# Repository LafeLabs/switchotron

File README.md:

# [SWITCHOTRON](https://github.com/lafelabs/switchotron/)

### [localhost](http://localhost/)

## 6 channel switch control code:

```

#include <Adafruit_NeoPixel.h>
#ifdef __AVR__
#endif

// Which pin on the Arduino is connected to the NeoPixels?
#define PIN        12 // On Trinket or Gemma, suggest changing this to 1

// How many NeoPixels are attached to the Arduino?
#define NUMPIXELS 6 // Popular NeoPixel ring size
//there are 8 neopixels but this code is for 6 used along with 6 buttons

// When setting up the NeoPixel library, we tell it how many pixels,  
// and which pin to use to send signals. Note that for older NeoPixel
// strips you might need to change the third parameter -- see the
// strandtest example for more information on possible values.
Adafruit_NeoPixel pixels(NUMPIXELS, PIN, NEO_GRB + NEO_KHZ800);

int analog = 0;
int delta = 100;
int mode = 1;//modes are 1,2,3,4,5, and 6 which are pixel 5,4,3,2,1, and 0 respectively

void setup() {
   Serial.begin(115200);

  // These lines are specifically to support the Adafruit Trinket 5V 16 MHz.
  // Any other board, you can remove this part (but no harm leaving it):
#if defined(__AVR_ATtiny85__) && (F_CPU == 16000000)
  clock_prescale_set(clock_div_1);
#endif
  // END of Trinket-specific code.

    pinMode(3,OUTPUT);
    pinMode(4,OUTPUT);
    pinMode(5,OUTPUT);
    pinMode(6,OUTPUT);
    pinMode(7,OUTPUT);
    pinMode(8,OUTPUT);

    digitalWrite(3,LOW);
    digitalWrite(4,LOW);
    digitalWrite(5,LOW);
    digitalWrite(6,LOW);
    digitalWrite(7,LOW);
    digitalWrite(8,LOW);

  pixels.begin(); // INITIALIZE NeoPixel strip object (REQUIRED)

}

void loop() {
  pixels.clear(); // Set all pixel colors to 'off'
  analog = analogRead(A0);
  // The first NeoPixel in a strand is #0, second is 1, all the way up
  // to the count of pixels minus one.
  
  if(analog > 1024 - delta){
    delay(1);
    analog = analogRead(A0);
    if(analog > 1023 - delta){
       mode = 1;      
    }
  }
  if(analog > 781 - delta && analog < 781 + delta){
    delay(5);
    analog = analogRead(A0);
    if(analog > 781 - delta && analog < 781 + delta){
         mode = 2; 
    }
  }
  if(analog > 593 - delta && analog < 593 + delta){
     delay(5);
     analog = analogRead(A0);

    if(analog > 593 - delta && analog < 593 + delta){
      mode = 3;    
    }
  }

  if(analog > 436 - delta && analog < 436 + delta){
     delay(1);
     analog = analogRead(A0);

    if(analog > 436 - delta && analog < 436 + delta){
      mode = 4;    
    }
  }

  if(analog > 296 - delta && analog < 296 + delta){
     delay(1);
     analog = analogRead(A0);

    if(analog > 296 - delta && analog < 296 + delta){
      mode = 5;    
    }
  }

  if(analog > 154 - delta && analog < 154 + delta){
     delay(1);
     analog = analogRead(A0);

    if(analog > 154 - delta && analog < 154 + delta){
      mode = 6;    
    }
  }

  if (Serial.available()) {

    //for more info on this code see http://adam-meyer.com/arduino/arduino-serial
    //read serial as ascii integer
        int ser = Serial.read();
    //    Serial.println(ser);
     if(ser == 49){    //ASCII for 1
      mode = 1;
     }
     if(ser == 50){    //ASCII for 2
      mode = 2;
     }
     if(ser == 51){    //ASCII for 3
      mode = 3;
     }
     if(ser == 52){    //ASCII for 4
      mode = 4;
     }
     if(ser == 53){    //ASCII for 5
      mode = 5;
     }
     if(ser == 54){    //ASCII for 6
      mode = 6;
     }

  }

  if(mode == 1){
    pixels.setPixelColor(0, pixels.Color(0, 0, 0));    
    pixels.setPixelColor(1, pixels.Color(0, 0, 0));    
    pixels.setPixelColor(2, pixels.Color(0, 0, 0));    
    pixels.setPixelColor(3, pixels.Color(0, 0, 0));    
    pixels.setPixelColor(4, pixels.Color(0, 0, 0));    
    pixels.setPixelColor(5, pixels.Color(255, 0, 0));    

    digitalWrite(3,HIGH);
    digitalWrite(4,LOW);
    digitalWrite(5,LOW);
    digitalWrite(6,LOW);
    digitalWrite(7,LOW);
    digitalWrite(8,LOW);
    
  }
  if(mode == 2){
    pixels.setPixelColor(0, pixels.Color(0, 0, 0));    
    pixels.setPixelColor(1, pixels.Color(0, 0, 0));    
    pixels.setPixelColor(2, pixels.Color(0, 0, 0));    
    pixels.setPixelColor(3, pixels.Color(0, 0, 0));    
    pixels.setPixelColor(4, pixels.Color(255, 165, 0));    
    pixels.setPixelColor(5, pixels.Color(0, 0, 0));    
    digitalWrite(3,LOW);
    digitalWrite(4,HIGH);
    digitalWrite(5,LOW);
    digitalWrite(6,LOW);
    digitalWrite(7,LOW);
    digitalWrite(8,LOW);
 
  }
  if(mode == 3){
    pixels.setPixelColor(0, pixels.Color(0, 0, 0));    
    pixels.setPixelColor(1, pixels.Color(0, 0, 0));    
    pixels.setPixelColor(2, pixels.Color(0, 0, 0));    
    pixels.setPixelColor(3, pixels.Color(255, 215, 0));    
    pixels.setPixelColor(4, pixels.Color(0, 0, 0));    
    pixels.setPixelColor(5, pixels.Color(0, 0, 0));    
    digitalWrite(3,LOW);
    digitalWrite(4,LOW);
    digitalWrite(5,HIGH);
    digitalWrite(6,LOW);
    digitalWrite(7,LOW);
    digitalWrite(8,LOW);
  }
  if(mode == 4){
    pixels.setPixelColor(0, pixels.Color(0, 0, 0));    
    pixels.setPixelColor(1, pixels.Color(0, 0, 0));    
    pixels.setPixelColor(2, pixels.Color(0, 255, 0));    
    pixels.setPixelColor(3, pixels.Color(0, 0, 0));    
    pixels.setPixelColor(4, pixels.Color(0, 0, 0));    
    pixels.setPixelColor(5, pixels.Color(0, 0, 0));    
    digitalWrite(3,LOW);
    digitalWrite(4,LOW);
    digitalWrite(5,LOW);
    digitalWrite(6,HIGH);
    digitalWrite(7,LOW);
    digitalWrite(8,LOW);
  }
  if(mode == 5){
    pixels.setPixelColor(0, pixels.Color(0, 0, 0));    
    pixels.setPixelColor(1, pixels.Color(0, 0, 255));    
    pixels.setPixelColor(2, pixels.Color(0, 0, 0));    
    pixels.setPixelColor(3, pixels.Color(0, 0, 0));    
    pixels.setPixelColor(4, pixels.Color(0, 0, 0));    
    pixels.setPixelColor(5, pixels.Color(0, 0, 0));    
    digitalWrite(3,LOW);
    digitalWrite(4,LOW);
    digitalWrite(5,LOW);
    digitalWrite(6,LOW);
    digitalWrite(7,HIGH);
    digitalWrite(8,LOW);
  }
  if(mode == 6){
    pixels.setPixelColor(0, pixels.Color(200, 0, 200));    
    pixels.setPixelColor(1, pixels.Color(0, 0, 0));    
    pixels.setPixelColor(2, pixels.Color(0, 0, 0));    
    pixels.setPixelColor(3, pixels.Color(0, 0, 0));    
    pixels.setPixelColor(4, pixels.Color(0, 0, 0));    
    pixels.setPixelColor(5, pixels.Color(0, 0, 0));    
    digitalWrite(3,LOW);
    digitalWrite(4,LOW);
    digitalWrite(5,LOW);
    digitalWrite(6,LOW);
    digitalWrite(7,LOW);
    digitalWrite(8,HIGH);
  }
  
  pixels.show();   // Send the updated pixel colors to the hardware.
  delay(1); // Pause before next pass through loop

    Serial.println(analog);

}
```
## 9 Channel Control Code:

```

#include <Adafruit_NeoPixel.h>
#ifdef __AVR__
#endif

// Which pin on the Arduino is connected to the NeoPixels?
#define PIN        12 // On Trinket or Gemma, suggest changing this to 1

// How many NeoPixels are attached to the Arduino?
#define NUMPIXELS 9 // 
//there are 9

// When setting up the NeoPixel library, we tell it how many pixels,  
// and which pin to use to send signals. Note that for older NeoPixel
// strips you might need to change the third parameter -- see the
// strandtest example for more information on possible values.
Adafruit_NeoPixel pixels(NUMPIXELS, PIN, NEO_GRB + NEO_KHZ800);

int analog = 0;
int delta = 20;
int mode = 1;//modes are 1,2,3,4,5,6,7,8,9 which are pixel 8,7,6,5,4,3,2,1, and 0 respectively

void setup() {
    Serial.begin(115200);

  // These lines are specifically to support the Adafruit Trinket 5V 16 MHz.
  // Any other board, you can remove this part (but no harm leaving it):
#if defined(__AVR_ATtiny85__) && (F_CPU == 16000000)
  clock_prescale_set(clock_div_1);
#endif
  // END of Trinket-specific code.

    pinMode(3,OUTPUT);
    pinMode(4,OUTPUT);
    pinMode(5,OUTPUT);
    pinMode(6,OUTPUT);
    pinMode(7,OUTPUT);
    pinMode(8,OUTPUT);

    digitalWrite(3,LOW);
    digitalWrite(4,LOW);
    digitalWrite(5,LOW);
    digitalWrite(6,LOW);
    digitalWrite(7,LOW);
    digitalWrite(8,LOW);

  pixels.begin(); // INITIALIZE NeoPixel strip object (REQUIRED)

}

void loop() {

  pixels.clear(); // Set all pixel colors to 'off'
  analog = analogRead(A0);
  // The first NeoPixel in a strand is #0, second is 1, all the way up
  // to the count of pixels minus one.
  
  if(analog > 1024 - delta){
    delay(1);
    analog = analogRead(A0);
    if(analog > 1023 - delta){
       mode = 1;      
    }
  }
  if(analog > 836 - delta && analog < 836 + delta){
    delay(5);
    analog = analogRead(A0);
    if(analog > 836 - delta && analog < 836 + delta){
         mode = 2; 
    }
  }
  if(analog > 690 - delta && analog < 690 + delta){
     delay(5);
     analog = analogRead(A0);

    if(analog > 690 - delta && analog < 690 + delta){
      mode = 3;    
    }
  }

  if(analog > 569 - delta && analog < 569 + delta){
     delay(1);
     analog = analogRead(A0);

    if(analog > 569 - delta && analog < 569 + delta){
      mode = 4;    
    }
  }

  if(analog > 464 - delta && analog < 464 + delta){
     delay(1);
     analog = analogRead(A0);

    if(analog > 464 - delta && analog < 464 + delta){
      mode = 5;    
    }
  }

  if(analog > 372 - delta && analog < 372 + delta){
     delay(1);
     analog = analogRead(A0);

    if(analog > 372 - delta && analog < 372 + delta){
      mode = 6;    
    }
  }

  if(analog > 283 - delta && analog < 283 + delta){
     delay(1);
     analog = analogRead(A0);

    if(analog > 283 - delta && analog < 283 + delta){
      mode = 7;    
    }
  }

  if(analog > 195 - delta && analog < 195 + delta){
     delay(1);
     analog = analogRead(A0);

    if(analog > 195 - delta && analog < 195 + delta){
      mode = 8;    
    }
  }

  if(analog > 103 - delta && analog < 103 + delta){
     delay(1);
     analog = analogRead(A0);

    if(analog > 103 - delta && analog < 103 + delta){
      mode = 9;    
    }
  }

  if (Serial.available()) {

    //for more info on this code see http://adam-meyer.com/arduino/arduino-serial
    //read serial as ascii integer
     int ser = Serial.read();
    //    Serial.println(ser);
     if(ser == 49){    //ASCII for 1
      mode = 1;
     }
     if(ser == 50){    //ASCII for 2
      mode = 2;
     }
     if(ser == 51){    //ASCII for 3
      mode = 3;
     }
     if(ser == 52){    //ASCII for 4
      mode = 4;
     }
     if(ser == 53){    //ASCII for 5
      mode = 5;
     }
     if(ser == 54){    //ASCII for 6
      mode = 6;
     }
     if(ser == 55){    //ASCII for 4
      mode = 7;
     }
     if(ser == 56){    //ASCII for 5
      mode = 8;
     }
     if(ser == 57){    //ASCII for 6
      mode = 9;
     }

  }

  if(mode == 1){
    pixels.setPixelColor(0, pixels.Color(0, 0, 0));    
    pixels.setPixelColor(1, pixels.Color(0, 0, 0));    
    pixels.setPixelColor(2, pixels.Color(0, 0, 0));    
    pixels.setPixelColor(3, pixels.Color(0, 0, 0));    
    pixels.setPixelColor(4, pixels.Color(0, 0, 0));    
    pixels.setPixelColor(5, pixels.Color(0, 0, 0));    
    pixels.setPixelColor(6, pixels.Color(0, 0, 0));    
    pixels.setPixelColor(7, pixels.Color(0, 0, 0));    
    pixels.setPixelColor(8, pixels.Color(255, 0, 0));    
    digitalWrite(3,HIGH);
    digitalWrite(4,LOW);
    digitalWrite(5,LOW);
    digitalWrite(6,HIGH);
    digitalWrite(7,LOW);
    digitalWrite(8,LOW);

  }
  if(mode == 2){
    pixels.setPixelColor(0, pixels.Color(0, 0, 0));    
    pixels.setPixelColor(1, pixels.Color(0, 0, 0));    
    pixels.setPixelColor(2, pixels.Color(0, 0, 0));    
    pixels.setPixelColor(3, pixels.Color(0, 0, 0));    
    pixels.setPixelColor(4, pixels.Color(0, 0, 0));    
    pixels.setPixelColor(5, pixels.Color(0, 0, 0));    
    pixels.setPixelColor(6, pixels.Color(0, 0, 0));    
    pixels.setPixelColor(7, pixels.Color(255, 0, 0));    
    pixels.setPixelColor(8, pixels.Color(0, 0, 0));    
    digitalWrite(3,HIGH);
    digitalWrite(4,LOW);
    digitalWrite(5,LOW);
    digitalWrite(6,LOW);
    digitalWrite(7,HIGH);
    digitalWrite(8,LOW);

  }
  if(mode == 3){
    pixels.setPixelColor(0, pixels.Color(0, 0, 0));    
    pixels.setPixelColor(1, pixels.Color(0, 0, 0));    
    pixels.setPixelColor(2, pixels.Color(0, 0, 0));    
    pixels.setPixelColor(3, pixels.Color(0, 0, 0));    
    pixels.setPixelColor(4, pixels.Color(0, 0, 0));    
    pixels.setPixelColor(5, pixels.Color(0, 0, 0));    
    pixels.setPixelColor(6, pixels.Color(255, 0, 0));    
    pixels.setPixelColor(7, pixels.Color(0, 0, 0));    
    pixels.setPixelColor(8, pixels.Color(0, 0, 0));    
    digitalWrite(3,HIGH);
    digitalWrite(4,LOW);
    digitalWrite(5,LOW);
    digitalWrite(6,LOW);
    digitalWrite(7,LOW);
    digitalWrite(8,HIGH);

  }
  if(mode == 4){
    pixels.setPixelColor(0, pixels.Color(0, 0, 0));    
    pixels.setPixelColor(1, pixels.Color(0, 0, 0));    
    pixels.setPixelColor(2, pixels.Color(0, 0, 0));    
    pixels.setPixelColor(3, pixels.Color(0, 0, 0));    
    pixels.setPixelColor(4, pixels.Color(0, 0, 0));    
    pixels.setPixelColor(5, pixels.Color(255, 0, 0));    
    pixels.setPixelColor(6, pixels.Color(0, 0, 0));    
    pixels.setPixelColor(7, pixels.Color(0, 0, 0));    
    pixels.setPixelColor(8, pixels.Color(0, 0, 0));    
    digitalWrite(3,LOW);
    digitalWrite(4,HIGH);
    digitalWrite(5,LOW);
    digitalWrite(6,HIGH);
    digitalWrite(7,LOW);
    digitalWrite(8,LOW);

  }
  if(mode == 5){
    pixels.setPixelColor(0, pixels.Color(0, 0, 0));    
    pixels.setPixelColor(1, pixels.Color(0, 0, 0));    
    pixels.setPixelColor(2, pixels.Color(0, 0, 0));    
    pixels.setPixelColor(3, pixels.Color(0, 0, 0));    
    pixels.setPixelColor(4, pixels.Color(255, 0, 0));    
    pixels.setPixelColor(5, pixels.Color(0, 0, 0));    
    pixels.setPixelColor(6, pixels.Color(0, 0, 0));    
    pixels.setPixelColor(7, pixels.Color(0, 0, 0));    
    pixels.setPixelColor(8, pixels.Color(0, 0, 0));    
    digitalWrite(3,LOW);
    digitalWrite(4,HIGH);
    digitalWrite(5,LOW);
    digitalWrite(6,LOW);
    digitalWrite(7,HIGH);
    digitalWrite(8,LOW);

  }
  if(mode == 6){
    pixels.setPixelColor(0, pixels.Color(0, 0, 0));    
    pixels.setPixelColor(1, pixels.Color(0, 0, 0));    
    pixels.setPixelColor(2, pixels.Color(0, 0, 0));    
    pixels.setPixelColor(3, pixels.Color(255, 0, 0));    
    pixels.setPixelColor(4, pixels.Color(0, 0, 0));    
    pixels.setPixelColor(5, pixels.Color(0, 0, 0));    
    pixels.setPixelColor(6, pixels.Color(0, 0, 0));    
    pixels.setPixelColor(7, pixels.Color(0, 0, 0));    
    pixels.setPixelColor(8, pixels.Color(0, 0, 0));    
    digitalWrite(3,LOW);
    digitalWrite(4,HIGH);
    digitalWrite(5,LOW);
    digitalWrite(6,LOW);
    digitalWrite(7,LOW);
    digitalWrite(8,HIGH);

  }

  if(mode == 7){
    pixels.setPixelColor(0, pixels.Color(0, 0, 0));    
    pixels.setPixelColor(1, pixels.Color(0, 0, 0));    
    pixels.setPixelColor(2, pixels.Color(255, 0, 0));    
    pixels.setPixelColor(3, pixels.Color(0, 0, 0));    
    pixels.setPixelColor(4, pixels.Color(0, 0, 0));    
    pixels.setPixelColor(5, pixels.Color(0, 0, 0));    
    pixels.setPixelColor(6, pixels.Color(0, 0, 0));    
    pixels.setPixelColor(7, pixels.Color(0, 0, 0));    
    pixels.setPixelColor(8, pixels.Color(0, 0, 0));    
    digitalWrite(3,LOW);
    digitalWrite(4,LOW);
    digitalWrite(5,HIGH);
    digitalWrite(6,HIGH);
    digitalWrite(7,LOW);
    digitalWrite(8,LOW);

 }
  if(mode == 8){
    pixels.setPixelColor(0, pixels.Color(0, 0, 0));    
    pixels.setPixelColor(1, pixels.Color(255, 0, 0));    
    pixels.setPixelColor(2, pixels.Color(0, 0, 0));    
    pixels.setPixelColor(3, pixels.Color(0, 0, 0));    
    pixels.setPixelColor(4, pixels.Color(0, 0, 0));    
    pixels.setPixelColor(5, pixels.Color(0, 0, 0));    
    pixels.setPixelColor(6, pixels.Color(0, 0, 0));    
    pixels.setPixelColor(7, pixels.Color(0, 0, 0));    
    pixels.setPixelColor(8, pixels.Color(0, 0, 0));    
    digitalWrite(3,LOW);
    digitalWrite(4,LOW);
    digitalWrite(5,HIGH);
    digitalWrite(6,LOW);
    digitalWrite(7,HIGH);
    digitalWrite(8,LOW);

  }
  if(mode == 9){
    pixels.setPixelColor(0, pixels.Color(255, 0, 0));    
    pixels.setPixelColor(1, pixels.Color(0, 0, 0));    
    pixels.setPixelColor(2, pixels.Color(0, 0, 0));    
    pixels.setPixelColor(3, pixels.Color(0, 0, 0));    
    pixels.setPixelColor(4, pixels.Color(0, 0, 0));    
    pixels.setPixelColor(5, pixels.Color(0, 0, 0));    
    pixels.setPixelColor(6, pixels.Color(0, 0, 0));    
    pixels.setPixelColor(7, pixels.Color(0, 0, 0));    
    pixels.setPixelColor(8, pixels.Color(0, 0, 0));    
    digitalWrite(3,LOW);
    digitalWrite(4,LOW);
    digitalWrite(5,HIGH);
    digitalWrite(6,LOW);
    digitalWrite(7,LOW);
    digitalWrite(8,HIGH);

  }

  pixels.show();   // Send the updated pixel colors to the hardware.
  delay(1); // Pause before next pass through loop

//    Serial.println(analog);

}

```

The switch as sign, using GEOMETRON.

This is a modular system of Arduino-based switch controllers for metrology.  The relay board is laid out on a 10 inch by 10 inch square, cut from acrylic or wood on a laser cutter or with a saw and drill.  

# UNO SHIELD BOARD

### EAGLE FILES

 - [switchotron-arduino-uno-shield-v1.brd](https://raw.githubusercontent.com/LafeLabs/switchotron/main/switchotron-arduino-uno-shield/switchotron-arduino-uno-shield-v1.brd)
 - [switchotron-arduino-uno-shield-v1.sch](https://raw.githubusercontent.com/LafeLabs/switchotron/main/switchotron-arduino-uno-shield/switchotron-arduino-uno-shield-v1.sch)

### GERBER FILES

 - [switchotron-arduino-uno-shield-v1-gerbers.zip](https://github.com/LafeLabs/switchotron/raw/main/switchotron-arduino-uno-shield/switchotron-arduino-uno-shield-v1-gerbers.zip)

### PART LINKS

 - [Audio Jack part link on Digikey](https://www.digikey.com/en/products/detail/cui-devices/MJ-3536N/281264)
 - [10 uF SMT capacitor in 0603 package link on Digikey](https://www.digikey.com/en/products/detail/samsung-electro-mechanics/CL10A106MP8NNNC/3887529)
 - [1000 uF electrolytic capacitor link on Digikey](https://www.digikey.com/en/products/detail/rubycon/35PX1000MEFC10X20/3563769)
 - [300 Ohm SMT resistor in 0603 package link on Digikey](https://www.digikey.com/en/products/detail/stackpole-electronics-inc/RMCF0603FT300R/1760765)
 - [1 megaohm SMT resistor in 0603 package link on digikey](https://www.digikey.com/en/products/detail/panasonic-electronic-components/ERJ-3EKF1004V/196033)
 - [10 kiloohm potentiometer Digikey link](https://www.digikey.com/en/products/detail/bourns-inc/PTV09A-4225F-B103/3781155)
 - [Switch link on digikey](https://www.digikey.com/en/products/detail/nkk-switches/B13AP/379100)
 - [rainbow colored Male 0.1" header pin kit from Digikey/Adafruit](https://www.digikey.com/en/products/detail/adafruit-industries-llc/4154/10123805)
 - [SAMTEC IDSS-05-D-03.00 5 pin cable](https://www.samtec.com/products/idss-05-d-03.00)
 - [SAMTEC IDSS-10-D-03.00 10 pin cable](https://www.samtec.com/products/idss-10-d-03.00)
 - [SAMTEC datasheet](https://www.mouser.com/datasheet/2/527/idmd-2508302.pdf)

# 3 BUTTONS 3 LIGHTS BOARD

This board turned out to have the WS2811 pad on the first version, which is wrong!  The neopixel boards are all now the WS2812B.  

here is the version 1 board showing how the neopixel doesn't fit:

WS2812 layout and pins:

#### EAGLE FILES

 - [switchotron-3buttons-3lights-v2.brd](https://raw.githubusercontent.com/LafeLabs/switchotron/main/switchotron-3buttons-3lights/switchotron-3buttons-3lights-v2.brd)
 - [switchotron-3buttons-3lights-v2.sch](https://raw.githubusercontent.com/LafeLabs/switchotron/main/switchotron-3buttons-3lights/switchotron-3buttons-3lights-v2.sch)

### GERBER FILES

 - [switchotron-3buttons-3lights-v2-gerbers.zip](https://github.com/LafeLabs/switchotron/raw/main/switchotron-3buttons-3lights/switchotron-3buttons-3lights-v2-gerbers.zip)

###  PARTS LINKS

 - [WS2812B LED NEOPIXELS](https://www.digikey.com/en/products/detail/sparkfun-electronics/COM-16347/11630204)
 - [10 uF Capacitors](https://www.digikey.com/en/products/detail/samsung-electro-mechanics/CL10A106MP8NNNC/3887529)
 - [10 k resistors](https://www.digikey.com/en/products/detail/stackpole-electronics-inc/RMCF0603FT10K0/1761235)
 - [buttons](https://www.digikey.com/en/products/detail/e-switch/TL59AF100Q/1144803)
 - [headers](https://www.digikey.com/en/products/detail/adafruit-industries-llc/4154/10123805)

# RELAY BOARD

### EAGLE FILES

 - [switchotron-relayboard-v1.brd](https://raw.githubusercontent.com/LafeLabs/switchotron/main/switchotron-relayboard/switchotron-relayboard-v1.brd)
 - [switchotron-relayboard-v1.sch](https://raw.githubusercontent.com/LafeLabs/switchotron/main/switchotron-relayboard/switchotron-relayboard-v1.sch)

### GERBER FILES

 - [switchotron-relayboard-v1-gerbers.zip](https://github.com/LafeLabs/switchotron/raw/main/switchotron-3buttons-3lights/switchotron-relayboard-v1-gerbers.zip)

### PARTS LINKS

 - [Audio Jack part link on Digikey](https://www.digikey.com/en/products/detail/cui-devices/MJ-3536N/281264)
 - [headers](https://www.digikey.com/en/products/detail/adafruit-industries-llc/4154/10123805)
 - [relays](https://www.digikey.com/en/products/detail/comus-international/3570-1331-051/7497098)

#### LASER CUTOUTS AND DIMENSIONS

CUT ALL SQUARES OUT 10 INCHES ON A SIDE:

CUT THIS OUT 19X7 INCHES:

ADD OR MODIFY HOLE POSITIONS AS NEEDED FOR BOARD WHICH ADAPTS TO FRIDGE CABLE.  

### ARDUINO BOARD DIMENSIONS AND HOLE LAYOUTS

### FASTENERS FROM MCMASTER CARR

 - [4-40 brass hex nuts](https://www.mcmaster.com/92671A005/)
 - [4-40 3/8" long brass pan head Phillips screws](https://www.mcmaster.com/94070A108/)

# ARDUINO CODE TO SWITCH BETWEEN THREE RELAY STATES

BUTTONS ARE 1,2,3 FROM LEFT TO RIGHT, AND ARE RED, GREEN, THEN BLUE LIGHTS.  

```

#include <Adafruit_NeoPixel.h>
#ifdef __AVR__
#endif

// Which pin on the Arduino is connected to the NeoPixels?
#define PIN        12 // On Trinket or Gemma, suggest changing this to 1

// How many NeoPixels are attached to the Arduino?
#define NUMPIXELS 3 // Popular NeoPixel ring size

// When setting up the NeoPixel library, we tell it how many pixels,
// and which pin to use to send signals. Note that for older NeoPixel
// strips you might need to change the third parameter -- see the
// strandtest example for more information on possible values.
Adafruit_NeoPixel pixels(NUMPIXELS, PIN, NEO_GRB + NEO_KHZ800);

int analog = 0;
int delta = 100;
int mode = 1;//modes are 1,2, and 3, which are pixel 2,1, and 0 respectively

void setup() {
      Serial.begin(115200);

  // These lines are specifically to support the Adafruit Trinket 5V 16 MHz.
  // Any other board, you can remove this part (but no harm leaving it):
#if defined(__AVR_ATtiny85__) && (F_CPU == 16000000)
  clock_prescale_set(clock_div_1);
#endif
  // END of Trinket-specific code.

    pinMode(3,OUTPUT);
    pinMode(4,OUTPUT);
    pinMode(5,OUTPUT);
    digitalWrite(3,HIGH);
    digitalWrite(4,LOW);
    digitalWrite(5,LOW);

  pixels.begin(); // INITIALIZE NeoPixel strip object (REQUIRED)

}

void loop() {
  pixels.clear(); // Set all pixel colors to 'off'
  analog = analogRead(A0);
  // The first NeoPixel in a strand is #0, second is 1, all the way up
  // to the count of pixels minus one.
  
  if(analog > 1024 - delta){
    delay(1);
    analog = analogRead(A0);
    if(analog > 1024 - delta){
       mode = 1;      
    }
  }
  if(analog > (2*1024/3) - delta && analog < (2*1024/3) + delta){
    delay(1);
    analog = analogRead(A0);
    if(analog > (2*1024/3) - delta && analog < (2*1024/3) + delta){
         mode = 2; 
    }
  }
  if(analog > (1*1024/3) - delta && analog < (1*1024/3) + delta){
     delay(1);
     analog = analogRead(A0);

    if(analog > (1*1024/3) - delta && analog < (1*1024/3) + delta){
      mode = 3;
    
  }

  }
  if(mode == 1){
    pixels.setPixelColor(0, pixels.Color(0, 0, 0));    
    pixels.setPixelColor(1, pixels.Color(0, 0, 0));    
    pixels.setPixelColor(2, pixels.Color(200, 0, 0));    
    digitalWrite(4,LOW);
    digitalWrite(5,LOW);
    digitalWrite(3,HIGH);

  }
  if(mode == 2){
    pixels.setPixelColor(0, pixels.Color(0, 0, 0));    
    pixels.setPixelColor(1, pixels.Color(0, 200, 0));    
    pixels.setPixelColor(2, pixels.Color(0, 0, 0));    
    digitalWrite(3,LOW);
    digitalWrite(5,LOW);
    digitalWrite(4,HIGH);
 
  }
  if(mode == 3){
    pixels.setPixelColor(0, pixels.Color(0, 0, 200));    
     pixels.setPixelColor(1, pixels.Color(0, 0, 0));    
    pixels.setPixelColor(2, pixels.Color(0, 0, 0));    
    digitalWrite(4,LOW);
    digitalWrite(3,LOW);
    digitalWrite(5,HIGH);

  }
  pixels.show();   // Send the updated pixel colors to the hardware.
  delay(1); // Pause before next pass through loop

    Serial.println(analog);

}
```

## 8 LED array, using 6 pixels and 6 buttons code

```

#include <Adafruit_NeoPixel.h>
#ifdef __AVR__
#endif

// Which pin on the Arduino is connected to the NeoPixels?
#define PIN        12 // On Trinket or Gemma, suggest changing this to 1

// How many NeoPixels are attached to the Arduino?
#define NUMPIXELS 8 // Popular NeoPixel ring size
//there are 8 neopixels but this code is for 6 used along with 6 buttons

// When setting up the NeoPixel library, we tell it how many pixels,  
// and which pin to use to send signals. Note that for older NeoPixel
// strips you might need to change the third parameter -- see the
// strandtest example for more information on possible values.
Adafruit_NeoPixel pixels(NUMPIXELS, PIN, NEO_GRB + NEO_KHZ800);

int analog = 0;
int delta = 100;
int mode = 1;//modes are 1,2,3,4,5, and 6 which are pixel 5,4,3,2,1, and 0 respectively

void setup() {
      Serial.begin(115200);

  // These lines are specifically to support the Adafruit Trinket 5V 16 MHz.
  // Any other board, you can remove this part (but no harm leaving it):
#if defined(__AVR_ATtiny85__) && (F_CPU == 16000000)
  clock_prescale_set(clock_div_1);
#endif
  // END of Trinket-specific code.

    pinMode(3,OUTPUT);
    pinMode(4,OUTPUT);
    pinMode(5,OUTPUT);
    pinMode(6,OUTPUT);
    pinMode(7,OUTPUT);
    pinMode(8,OUTPUT);

    digitalWrite(3,LOW);
    digitalWrite(4,LOW);
    digitalWrite(5,LOW);
    digitalWrite(6,LOW);
    digitalWrite(7,LOW);
    digitalWrite(8,LOW);

  pixels.begin(); // INITIALIZE NeoPixel strip object (REQUIRED)

}

void loop() {
  pixels.clear(); // Set all pixel colors to 'off'
  analog = analogRead(A0);
  // The first NeoPixel in a strand is #0, second is 1, all the way up
  // to the count of pixels minus one.
  
  if(analog > 1024 - delta){
    delay(1);
    analog = analogRead(A0);
    if(analog > 1023 - delta){
       mode = 1;      
    }
  }
  if(analog > 781 - delta && analog < 781 + delta){
    delay(5);
    analog = analogRead(A0);
    if(analog > 781 - delta && analog < 781 + delta){
         mode = 2; 
    }
  }
  if(analog > 593 - delta && analog < 593 + delta){
     delay(5);
     analog = analogRead(A0);

    if(analog > 593 - delta && analog < 593 + delta){
      mode = 3;    
    }
  }

  if(analog > 436 - delta && analog < 436 + delta){
     delay(1);
     analog = analogRead(A0);

    if(analog > 436 - delta && analog < 436 + delta){
      mode = 4;    
    }
  }

  if(analog > 296 - delta && analog < 296 + delta){
     delay(1);
     analog = analogRead(A0);

    if(analog > 296 - delta && analog < 296 + delta){
      mode = 5;    
    }
  }

  if(analog > 154 - delta && analog < 154 + delta){
     delay(1);
     analog = analogRead(A0);

    if(analog > 154 - delta && analog < 154 + delta){
      mode = 6;    
    }
  }

  if(mode == 1){
    pixels.setPixelColor(0, pixels.Color(0, 0, 0));    
    pixels.setPixelColor(1, pixels.Color(0, 0, 0));    
    pixels.setPixelColor(2, pixels.Color(0, 0, 0));    
    pixels.setPixelColor(3, pixels.Color(0, 0, 0));    
    pixels.setPixelColor(4, pixels.Color(0, 0, 0));    
    pixels.setPixelColor(5, pixels.Color(255, 0, 0));    

    digitalWrite(3,LOW);
    digitalWrite(4,LOW);
    digitalWrite(5,LOW);
    digitalWrite(6,LOW);
    digitalWrite(7,LOW);
    digitalWrite(8,LOW);
    digitalWrite(3,HIGH);
    
  }
  if(mode == 2){
    pixels.setPixelColor(0, pixels.Color(0, 0, 0));    
    pixels.setPixelColor(1, pixels.Color(0, 0, 0));    
    pixels.setPixelColor(2, pixels.Color(0, 0, 0));    
    pixels.setPixelColor(3, pixels.Color(0, 0, 0));    
    pixels.setPixelColor(4, pixels.Color(255, 165, 0));    
    pixels.setPixelColor(5, pixels.Color(0, 0, 0));    
    digitalWrite(3,LOW);
    digitalWrite(4,LOW);
    digitalWrite(5,LOW);
    digitalWrite(6,LOW);
    digitalWrite(7,LOW);
    digitalWrite(8,LOW);
    digitalWrite(4,HIGH);
 
  }
  if(mode == 3){
    pixels.setPixelColor(0, pixels.Color(0, 0, 0));    
    pixels.setPixelColor(1, pixels.Color(0, 0, 0));    
    pixels.setPixelColor(2, pixels.Color(0, 0, 0));    
    pixels.setPixelColor(3, pixels.Color(255, 215, 0));    
    pixels.setPixelColor(4, pixels.Color(0, 0, 0));    
    pixels.setPixelColor(5, pixels.Color(0, 0, 0));    
    digitalWrite(3,LOW);
    digitalWrite(4,LOW);
    digitalWrite(5,LOW);
    digitalWrite(6,LOW);
    digitalWrite(7,LOW);
    digitalWrite(8,LOW);
    digitalWrite(5,HIGH);   
  }
  if(mode == 4){
    pixels.setPixelColor(0, pixels.Color(0, 0, 0));    
    pixels.setPixelColor(1, pixels.Color(0, 0, 0));    
    pixels.setPixelColor(2, pixels.Color(0, 255, 0));    
    pixels.setPixelColor(3, pixels.Color(0, 0, 0));    
    pixels.setPixelColor(4, pixels.Color(0, 0, 0));    
    pixels.setPixelColor(5, pixels.Color(0, 0, 0));    
    digitalWrite(3,LOW);
    digitalWrite(4,LOW);
    digitalWrite(5,LOW);
    digitalWrite(6,LOW);
    digitalWrite(7,LOW);
    digitalWrite(8,LOW);
    digitalWrite(6,HIGH);   
  }
  if(mode == 5){
    pixels.setPixelColor(0, pixels.Color(0, 0, 0));    
    pixels.setPixelColor(1, pixels.Color(0, 0, 255));    
    pixels.setPixelColor(2, pixels.Color(0, 0, 0));    
    pixels.setPixelColor(3, pixels.Color(0, 0, 0));    
    pixels.setPixelColor(4, pixels.Color(0, 0, 0));    
    pixels.setPixelColor(5, pixels.Color(0, 0, 0));    
    digitalWrite(3,LOW);
    digitalWrite(4,LOW);
    digitalWrite(5,LOW);
    digitalWrite(6,LOW);
    digitalWrite(7,LOW);
    digitalWrite(8,LOW);
    digitalWrite(7,HIGH);   
  }
  if(mode == 6){
    pixels.setPixelColor(0, pixels.Color(200, 0, 200));    
    pixels.setPixelColor(1, pixels.Color(0, 0, 0));    
    pixels.setPixelColor(2, pixels.Color(0, 0, 0));    
    pixels.setPixelColor(3, pixels.Color(0, 0, 0));    
    pixels.setPixelColor(4, pixels.Color(0, 0, 0));    
    pixels.setPixelColor(5, pixels.Color(0, 0, 0));    
    digitalWrite(3,LOW);
    digitalWrite(4,LOW);
    digitalWrite(5,LOW);
    digitalWrite(6,LOW);
    digitalWrite(7,LOW);
    digitalWrite(8,LOW);
    digitalWrite(8,HIGH);   
  }
  
  pixels.show();   // Send the updated pixel colors to the hardware.
  delay(1); // Pause before next pass through loop

    Serial.println(analog);

}

```

# Synth code with potentiometer

```

/*  Example playing a sinewave at a set frequency,
    using Mozzi sonification library.

DIRT SYNTH IS JUST SINE WAVE WITH FREQUENCY BASED ON AN ANALOG VOLTAGE ON THE CIRCUIT BOARD

    Demonstrates the use of Oscil to play a wavetable.

    Circuit: Audio output on digital pin 9 on a Uno or similar, or
    DAC/A14 on Teensy 3.1, or
    check the README or http://sensorium.github.io/Mozzi/

    Mozzi documentation/API
    https://sensorium.github.io/Mozzi/doc/html/index.html

    Mozzi help/discussion/announcements:
    https://groups.google.com/forum/#!forum/mozzi-users

    Tim Barrass 2012, CC by-nc-sa.
*/

int voltage = 0;
#include <Adafruit_NeoPixel.h>

#include <MozziGuts.h>
#include <Oscil.h> // oscillator template
#include <tables/sin2048_int8.h> // sine table for oscillator

// use: Oscil <table_size, update_rate> oscilName (wavetable), look in .h file of table #included above
Oscil <SIN2048_NUM_CELLS, AUDIO_RATE> aSin(SIN2048_DATA);

// use #define for CONTROL_RATE, not a constant
#define CONTROL_RATE 64 // Hz, powers of 2 are most reliable

void setup(){
  startMozzi(CONTROL_RATE); // :)
  aSin.setFreq(2600); // set the frequency 2600 HZ! HACK THE PLANET!
    pinMode(9,OUTPUT); 

}

void updateControl(){
  // put changing controls in here
}

AudioOutput_t updateAudio(){
  return MonoOutput::from8Bit(aSin.next()); // return an int signal centred around 0
}

void loop(){
  
  voltage = analogRead(A0);
  aSin.setFreq(440 + 3*voltage);  
  audioHook(); // required here
  
}
```

# CODE FOR 9 LINE CONTROLLER: 9 PIXELS, 9 BUTTONS

```

#include <Adafruit_NeoPixel.h>
#ifdef __AVR__
#endif

// Which pin on the Arduino is connected to the NeoPixels?
#define PIN        12 // On Trinket or Gemma, suggest changing this to 1

// How many NeoPixels are attached to the Arduino?
#define NUMPIXELS 9 // 
//there are 9

// When setting up the NeoPixel library, we tell it how many pixels,  
// and which pin to use to send signals. Note that for older NeoPixel
// strips you might need to change the third parameter -- see the
// strandtest example for more information on possible values.
Adafruit_NeoPixel pixels(NUMPIXELS, PIN, NEO_GRB + NEO_KHZ800);

int analog = 0;
int delta = 20;
int mode = 1;//modes are 1,2,3,4,5,6,7,8,9 which are pixel 8,7,6,5,4,3,2,1, and 0 respectively

void setup() {
      Serial.begin(115200);

  // These lines are specifically to support the Adafruit Trinket 5V 16 MHz.
  // Any other board, you can remove this part (but no harm leaving it):
#if defined(__AVR_ATtiny85__) && (F_CPU == 16000000)
  clock_prescale_set(clock_div_1);
#endif
  // END of Trinket-specific code.

    pinMode(3,OUTPUT);
    pinMode(4,OUTPUT);
    pinMode(5,OUTPUT);
    pinMode(6,OUTPUT);
    pinMode(7,OUTPUT);
    pinMode(8,OUTPUT);

    digitalWrite(3,LOW);
    digitalWrite(4,LOW);
    digitalWrite(5,LOW);
    digitalWrite(6,LOW);
    digitalWrite(7,LOW);
    digitalWrite(8,LOW);

  pixels.begin(); // INITIALIZE NeoPixel strip object (REQUIRED)

}

void loop() {
  pixels.clear(); // Set all pixel colors to 'off'
  analog = analogRead(A0);
  // The first NeoPixel in a strand is #0, second is 1, all the way up
  // to the count of pixels minus one.
  
  if(analog > 1024 - delta){
    delay(1);
    analog = analogRead(A0);
    if(analog > 1023 - delta){
       mode = 1;      
    }
  }
  if(analog > 836 - delta && analog < 836 + delta){
    delay(5);
    analog = analogRead(A0);
    if(analog > 836 - delta && analog < 836 + delta){
         mode = 2; 
    }
  }
  if(analog > 690 - delta && analog < 690 + delta){
     delay(5);
     analog = analogRead(A0);

    if(analog > 690 - delta && analog < 690 + delta){
      mode = 3;    
    }
  }

  if(analog > 569 - delta && analog < 569 + delta){
     delay(1);
     analog = analogRead(A0);

    if(analog > 569 - delta && analog < 569 + delta){
      mode = 4;    
    }
  }

  if(analog > 464 - delta && analog < 464 + delta){
     delay(1);
     analog = analogRead(A0);

    if(analog > 464 - delta && analog < 464 + delta){
      mode = 5;    
    }
  }

  if(analog > 372 - delta && analog < 372 + delta){
     delay(1);
     analog = analogRead(A0);

    if(analog > 372 - delta && analog < 372 + delta){
      mode = 6;    
    }
  }

  if(analog > 283 - delta && analog < 283 + delta){
     delay(1);
     analog = analogRead(A0);

    if(analog > 283 - delta && analog < 283 + delta){
      mode = 7;    
    }
  }

  if(analog > 195 - delta && analog < 195 + delta){
     delay(1);
     analog = analogRead(A0);

    if(analog > 195 - delta && analog < 195 + delta){
      mode = 8;    
    }
  }

  if(analog > 103 - delta && analog < 103 + delta){
     delay(1);
     analog = analogRead(A0);

    if(analog > 103 - delta && analog < 103 + delta){
      mode = 9;    
    }
  }

  if(mode == 1){
    pixels.setPixelColor(0, pixels.Color(0, 0, 0));    
    pixels.setPixelColor(1, pixels.Color(0, 0, 0));    
    pixels.setPixelColor(2, pixels.Color(0, 0, 0));    
    pixels.setPixelColor(3, pixels.Color(0, 0, 0));    
    pixels.setPixelColor(4, pixels.Color(0, 0, 0));    
    pixels.setPixelColor(5, pixels.Color(0, 0, 0));    
    pixels.setPixelColor(6, pixels.Color(0, 0, 0));    
    pixels.setPixelColor(7, pixels.Color(0, 0, 0));    
    pixels.setPixelColor(8, pixels.Color(255, 0, 0));    

  }
  if(mode == 2){
    pixels.setPixelColor(0, pixels.Color(0, 0, 0));    
    pixels.setPixelColor(1, pixels.Color(0, 0, 0));    
    pixels.setPixelColor(2, pixels.Color(0, 0, 0));    
    pixels.setPixelColor(3, pixels.Color(0, 0, 0));    
    pixels.setPixelColor(4, pixels.Color(0, 0, 0));    
    pixels.setPixelColor(5, pixels.Color(0, 0, 0));    
    pixels.setPixelColor(6, pixels.Color(0, 0, 0));    
    pixels.setPixelColor(7, pixels.Color(255, 0, 0));    
    pixels.setPixelColor(8, pixels.Color(0, 0, 0));    

  }
  if(mode == 3){
    pixels.setPixelColor(0, pixels.Color(0, 0, 0));    
    pixels.setPixelColor(1, pixels.Color(0, 0, 0));    
    pixels.setPixelColor(2, pixels.Color(0, 0, 0));    
    pixels.setPixelColor(3, pixels.Color(0, 0, 0));    
    pixels.setPixelColor(4, pixels.Color(0, 0, 0));    
    pixels.setPixelColor(5, pixels.Color(0, 0, 0));    
    pixels.setPixelColor(6, pixels.Color(255, 0, 0));    
    pixels.setPixelColor(7, pixels.Color(0, 0, 0));    
    pixels.setPixelColor(8, pixels.Color(0, 0, 0));    

  }
  if(mode == 4){
    pixels.setPixelColor(0, pixels.Color(0, 0, 0));    
    pixels.setPixelColor(1, pixels.Color(0, 0, 0));    
    pixels.setPixelColor(2, pixels.Color(0, 0, 0));    
    pixels.setPixelColor(3, pixels.Color(0, 0, 0));    
    pixels.setPixelColor(4, pixels.Color(0, 0, 0));    
    pixels.setPixelColor(5, pixels.Color(255, 0, 0));    
    pixels.setPixelColor(6, pixels.Color(0, 0, 0));    
    pixels.setPixelColor(7, pixels.Color(0, 0, 0));    
    pixels.setPixelColor(8, pixels.Color(0, 0, 0));    

  }
  if(mode == 5){
    pixels.setPixelColor(0, pixels.Color(0, 0, 0));    
    pixels.setPixelColor(1, pixels.Color(0, 0, 0));    
    pixels.setPixelColor(2, pixels.Color(0, 0, 0));    
    pixels.setPixelColor(3, pixels.Color(0, 0, 0));    
    pixels.setPixelColor(4, pixels.Color(255, 0, 0));    
    pixels.setPixelColor(5, pixels.Color(0, 0, 0));    
    pixels.setPixelColor(6, pixels.Color(0, 0, 0));    
    pixels.setPixelColor(7, pixels.Color(0, 0, 0));    
    pixels.setPixelColor(8, pixels.Color(0, 0, 0));    

  }
  if(mode == 6){
    pixels.setPixelColor(0, pixels.Color(0, 0, 0));    
    pixels.setPixelColor(1, pixels.Color(0, 0, 0));    
    pixels.setPixelColor(2, pixels.Color(0, 0, 0));    
    pixels.setPixelColor(3, pixels.Color(255, 0, 0));    
    pixels.setPixelColor(4, pixels.Color(0, 0, 0));    
    pixels.setPixelColor(5, pixels.Color(0, 0, 0));    
    pixels.setPixelColor(6, pixels.Color(0, 0, 0));    
    pixels.setPixelColor(7, pixels.Color(0, 0, 0));    
    pixels.setPixelColor(8, pixels.Color(0, 0, 0));    

  }

  if(mode == 7){
    pixels.setPixelColor(0, pixels.Color(0, 0, 0));    
    pixels.setPixelColor(1, pixels.Color(0, 0, 0));    
    pixels.setPixelColor(2, pixels.Color(255, 0, 0));    
    pixels.setPixelColor(3, pixels.Color(0, 0, 0));    
    pixels.setPixelColor(4, pixels.Color(0, 0, 0));    
    pixels.setPixelColor(5, pixels.Color(0, 0, 0));    
    pixels.setPixelColor(6, pixels.Color(0, 0, 0));    
    pixels.setPixelColor(7, pixels.Color(0, 0, 0));    
    pixels.setPixelColor(8, pixels.Color(0, 0, 0));    

 }
  if(mode == 8){
    pixels.setPixelColor(0, pixels.Color(0, 0, 0));    
    pixels.setPixelColor(1, pixels.Color(255, 0, 0));    
    pixels.setPixelColor(2, pixels.Color(0, 0, 0));    
    pixels.setPixelColor(3, pixels.Color(0, 0, 0));    
    pixels.setPixelColor(4, pixels.Color(0, 0, 0));    
    pixels.setPixelColor(5, pixels.Color(0, 0, 0));    
    pixels.setPixelColor(6, pixels.Color(0, 0, 0));    
    pixels.setPixelColor(7, pixels.Color(0, 0, 0));    
    pixels.setPixelColor(8, pixels.Color(0, 0, 0));    

  }
  if(mode == 9){
    pixels.setPixelColor(0, pixels.Color(255, 0, 0));    
    pixels.setPixelColor(1, pixels.Color(0, 0, 0));    
    pixels.setPixelColor(2, pixels.Color(0, 0, 0));    
    pixels.setPixelColor(3, pixels.Color(0, 0, 0));    
    pixels.setPixelColor(4, pixels.Color(0, 0, 0));    
    pixels.setPixelColor(5, pixels.Color(0, 0, 0));    
    pixels.setPixelColor(6, pixels.Color(0, 0, 0));    
    pixels.setPixelColor(7, pixels.Color(0, 0, 0));    
    pixels.setPixelColor(8, pixels.Color(0, 0, 0));    

  }

  pixels.show();   // Send the updated pixel colors to the hardware.
  delay(1); // Pause before next pass through loop

    Serial.println(analog);

}
```

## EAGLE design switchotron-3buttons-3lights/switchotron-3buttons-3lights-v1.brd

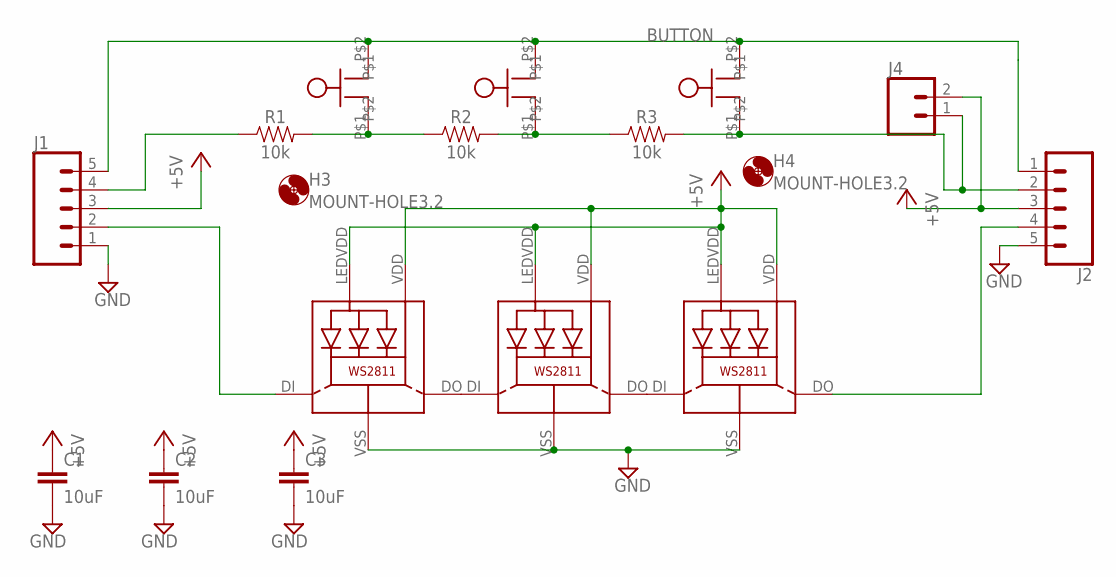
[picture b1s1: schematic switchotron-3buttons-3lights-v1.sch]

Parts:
C1, C2, C3: 10uF; 0603
H3, H4: MOUNT-HOLE3.2; 3,2
J1, J2: CONN_05; 1X05
J4: CONN_02; 1X02
LED1, LED2, LED8: WS28115050
R1, R2, R3: 10k; 0603
U$1, U$4, U$5: BUTTON

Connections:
+5V: C1.1, C2.1, C3.1, J1.3, J2.3, J4.2, LED1.LEDVDD, LED1.VDD, LED2.LEDVDD, LED2.VDD, LED8.LEDVDD, LED8.VDD
BUTTON: J1.5, J2.1, U$1.P$2, U$4.P$2, U$5.P$2
GND: C1.2, C2.2, C3.2, J1.1, J2.5, LED1.VSS (GND), LED2.VSS (GND), LED8.VSS (GND)
unnamed: LED1.DO, LED2.DI
unnamed: R1.2, R2.1, U$1.P$1
unnamed: R2.2, R3.1, U$4.P$1
unnamed: J2.2, J4.1, R3.2, U$5.P$1
unnamed: J1.4, R1.1
unnamed: LED2.DO, LED8.DI
unnamed: J1.2, LED1.DI
unnamed: J2.4, LED8.DO

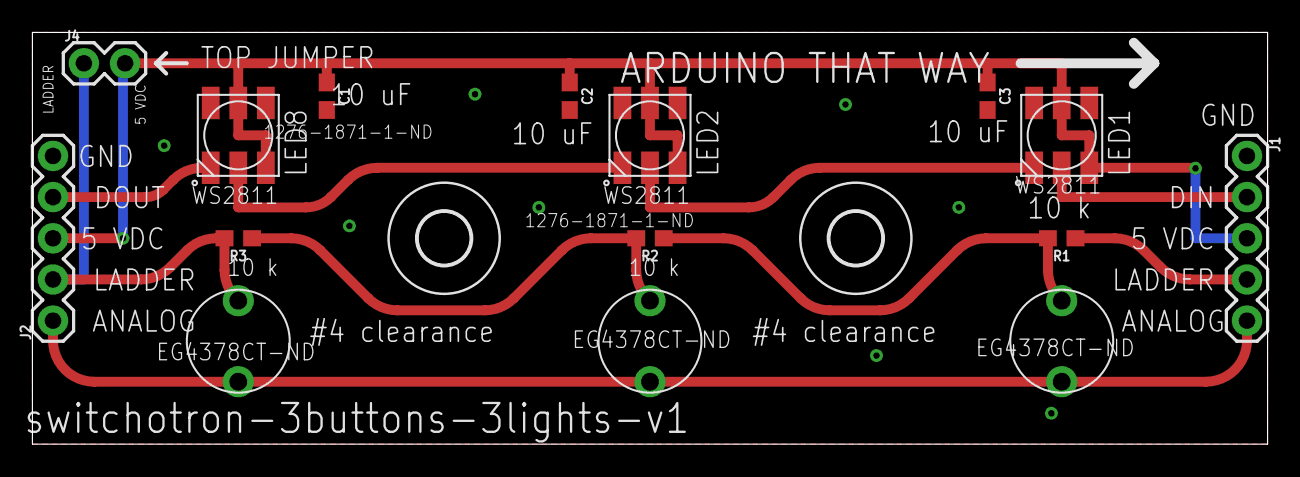
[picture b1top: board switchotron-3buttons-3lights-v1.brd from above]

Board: 2 copper layers, 76.2 x 25.4 mm, 17 parts (0 on the bottom side), 11 nets.

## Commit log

2023-12-24 switchotron is a system for controlling switches
2023-12-24 this is now self-replicating media
2023-12-24 adding more mechanicals
2023-12-24 more mechanicals
2023-12-24 uno mounting hole documentation
2023-12-24 added circular hole version of panel cutout
2023-12-24 update style to make more generic, not cardboard
2023-12-24 adding schematics
2023-12-24 more schematics
2023-12-24 still more schematics
2023-12-24 added qr codes
2023-12-25 round corners added, lots of readme updates
2023-12-25 more mechanicals design, now for mems switches controlled from rack mount
2023-12-25 mems driver draft board
2023-12-25 mems driver design work
2024-01-06 new version of 3 button 3 light board with WS2812B instead of WS2811
2024-01-06 images for the documentation to document the versioning of the board with the LEDs
2024-01-06 updated readme and images
2024-01-07 moved the LEDs up to 0.75 inches y axis position
2024-01-15 UPDATE README AND ALSO WORKING ON BILL OF MATERIALS FOR PCBA
2024-01-27 UPDATE CODE
2024-02-08 signal topology diagrams added as global images, both vector and bitmap
2024-02-08 switches
2024-02-15 the code now has serial control as well as buttons, no mode switch needed
2024-04-03 arduino code, copies of tested recently code

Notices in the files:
parts and their libraries:
microbuilder: This work is placed in the public domain, and may be freely used for commercial and non-commercial work with the following conditions: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
SparkFun-Resistors: Licensing: Creative Commons ShareAlike 4.0 International - https://creativecommons.org/licenses/by-sa/4.0
